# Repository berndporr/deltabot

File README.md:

# The Delta Bot

## What is the Delta Bot?
The Delta Bot is an open-source DIY robot AI platform that uses Radxa's single board computer, 

 - the [Rock 5B+](https://radxa.com/products/rock5/5b/),
 - Parallax's [Continuous Rotation Servo Motors](https://www.parallax.com/product/parallax-continuous-rotation-servo-factory-centered/),
 - C1 LIDAR https://github.com/berndporr/c1lidar and
 - Raspberry PI V2 camera

## Hardware

### Schematics
For details on the DeltaBot schematic, pcb, and footprint library refer to the subfolder [schematic_files](schematic_files).

### Connectors

Plug the right motor into J4, the left motor into J3 and the LIDAR into J2.

### Additional Mechanical Parts
Additional Mechanical Parts were designed in CAD and can be accessed [here](additional_files/deltabot.f3z):

In particular the "stage" which holds the power bank.

## Software

### Install ARMbian

Download from
https://www.armbian.com/rock-5b/
the image "Armbian 25.8.2 Bookworm Minimal / IOT".
the 
Call `armbian-config`:
  - upgrade to Debian "trixie"
  - Make sure you have kernel 26.2.1 Armbian Linux vendor headers 6.1.115-vendor-rk35xx

### PWM motor drivers

Start `sudo nano /boot/armbianEnv.txt`, identify these lines and add/edit them that
they look like these:

```
console=display
overlay_prefix=
overlays=rk3588-pwm14-m0 rk3588-pwm8-m0
```

This enables the UART and PWM on the pins 33 and 34 on the 40 pin header.

Create the group `gpio`:

```
groupadd gpio
```
and add yourself and other users to it who want to write to the PWM device.

Copy the file [90-gpio.rules](90-gpio.rules) to `/etc/udev/rules.d/`. This will
make sure that the PWM can accessed by any user who's in the gpio group.

The library and example programs how to control the motors are in [wheeleddrive](wheeleddrive).

### LIDAR

Enable the UART for serial communication. Start `sudo nano /boot/armbianEnv.txt`, identify these lines and add `rk3588-uart2-m0` to overlays.

```
overlay_prefix=
overlays=rk3588-uart2-m0
```

Add yourself to the group `dialout` to access /dev/tty*.

The driver and example programs are here: https://github.com/berndporr/c1lidar

### Raspberry PI V2 Cameras

The 1st RPI V2 camera has already a device overlay (`rock-5b-rpi-camera-v2`). The device overlay for the 2nd camera
needs to be compiled from source:

```
cpp -nostdinc -I /usr/src/linux-headers-6.1.115-vendor-rk35xx/include/ -undef -x assembler-with-cpp rock-5b-plus-cam1-rpi-camera-v2.dts > cam1.dts
dtc -@ -I dts -O dtb -o /tmp/rock-5b-plus-cam1-rpi-camera-v2.dtbo cam1.dts
cp /tmp/rock-5b-plus-cam1-rpi-camera-v2.dtbo /boot/dtb-6.1.115-vendor-rk35xx/rockchip/overlay/
```

Add this to the overlays in `armbianEnv.tex`:
```
overlays=rk3588-pwm14-m0 rk3588-pwm8-m0 rk3588-uart2-m0 rock-5b-rpi-camera-v2 rock-5b-plus-cam1-rpi-camera-v2
```

and reboot.

If all goes well both cameras will show up as:

```
media-ctl -p -d 0

rkcif (platform:rkcif-mipi-lvds2):
	/dev/video0
	/dev/video1
...
	/dev/media0

rkcif (platform:rkcif-mipi-lvds4):
	/dev/video11
	/dev/video12
...
	/dev/video21
	/dev/media1
```

which are the raw devices outputting Bayer patterns. The media device 1 is for the 2nd camera raw processing chain.

The media devices 2 and 3 are the Image Signal Processing chains which decode the images into YUV or Grey images.

To config the cameras you need to config V4L subdevices:

```
v4l2-ctl --device=/dev/v4l-subdev2 -L
v4l2-ctl --device=/dev/v4l-subdev7 -L

User Controls

                       exposure 0x00980911 (int)    : min=0 max=4095 step=1 default=1575 value=1575
                           gain 0x00980913 (int)    : min=256 max=43663 step=1 default=256 value=21960
                horizontal_flip 0x00980914 (bool)   : default=0 value=1
                  vertical_flip 0x00980915 (bool)   : default=0 value=1
```

[See the demo dual camera viewer](opencv-camera-callback) how it's all done in C++!

A fixed two-camera mount for repeatable stereo geometry is available in
[additional_files/stereo_camera_mount](additional_files/stereo_camera_mount).

The dual-camera viewer also applies a colour correction for the ROCK 5 Raspberry Pi Camera V2 setup.

## Credits
- Saleh AlMulla - 2721704A@student.gla.ac.uk
- Bernd Porr -  bernd.porr@glasgow.ac.uk
- Yixuan Zha - 2974642Z@student.gla.ac.uk

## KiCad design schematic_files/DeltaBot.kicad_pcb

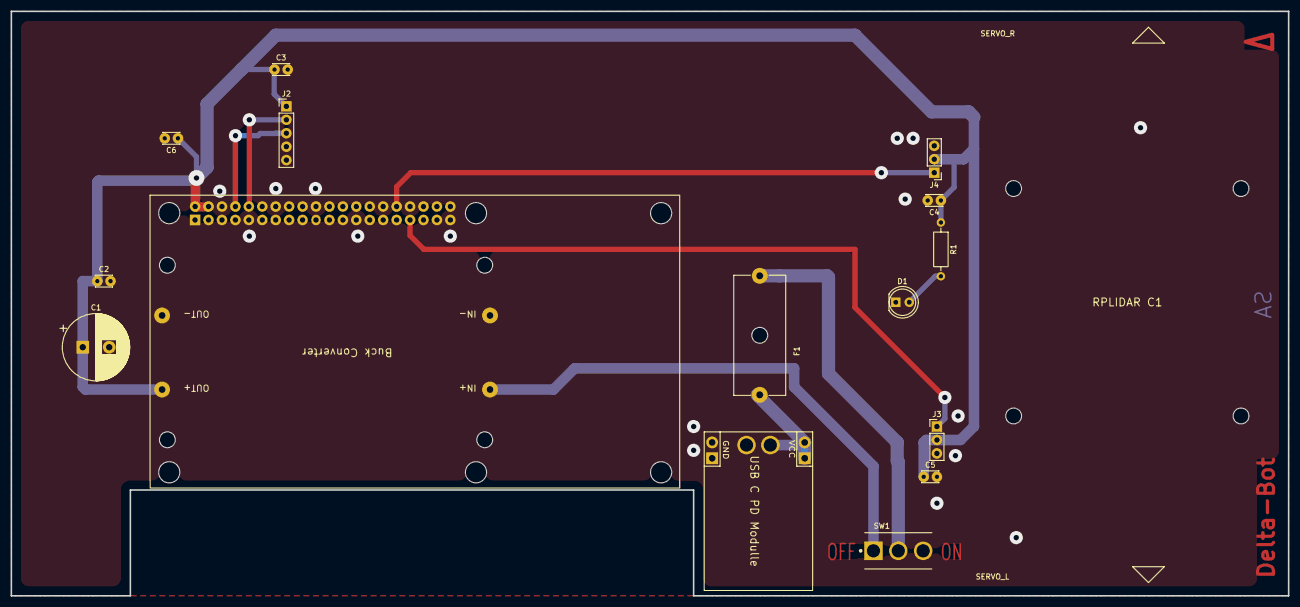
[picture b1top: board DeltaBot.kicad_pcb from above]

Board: 2 copper layers, 241.5 x 110.5 mm, 17 parts (1 on the bottom side), 10 nets.

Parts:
C1: 2200uF; CP_Radial_D12.5mm_P5.00mm
C2, C3, C4, C5, C6: 1uF; C_Disc_D3.0mm_W2.0mm_P2.50mm
D1: LED; LED_D5.0mm_Clear
F1: Fuse; Fuseholder_Cylinder-5x20mm_Schurter_0031_8201_Horizontal_Op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
J1: USB C PD Modulle; USB_C
J2: Conn_01x05; PinHeader_1x05_P2.54mm_Vertical
J3: MOTOR_L; PinHeader_1x03_P2.54mm_Vertical
J4: MOTOR_R; PinHeader_1x03_P2.54mm_Vertical
R1: 330R; R_Axial_DIN0207_L6.3mm_D2.5mm_P10.16mm_Horizontal
SW1: SW_SPDT; TE_4-1825136-5
U1: RPLIDAR C1
U1#2: Radxa_ROCK5B; ROCK_5B
U2: Buck Converter; BUCK_CONV

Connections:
+5V: C1.1, C2.1, C3.1, C4.1, C5.1, C6.1, J2.1, J3.2, J4.2, R1.1, U1#2.2 (5V1), U1#2.4 (5V2), U2.3 (OUT+)
+9V: SW1.1 (A), U2.1 (IN+)
GND: C1.2, C2.2, C3.2, C4.2, C5.2, C6.2, D1.1 (K), J1.2 (GND), J1.4 (GND), J2.4, J3.3, J4.3, U1#2.6 (GND1), U1#2.9 (GND8), U1#2.14 (GND2), U1#2.20 (GND3), U1#2.25 (GND7), U1#2.30 (GND4), U1#2.34 (GND5), U1#2.39 (GND6), U2.2 (IN-), U2.4 (OUT-)
LIDAR_RX: J2.3, U1#2.8 (GPIO4_C3)
LIDAR_TX: J2.2, U1#2.10 (GPIO4_C4)
unnamed: D1.2 (A), R1.2
unnamed: F1.2, J1.1 (VCC), J1.3 (VCC)
unnamed: F1.1, SW1.2 (B)
PWM_L: J3.1, U1#2.33 (GPIO2_B4)
PWM_R: J4.1, U1#2.32 (GPIO3_C0)

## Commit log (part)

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2026-02-01 Got rid of the scripts
2026-02-01 Added new photo
2026-02-01 Removed old files
2026-02-01 Removed the camera bits
2026-02-01 Added info of how to add the C1 LIDAR.
2026-02-01 Fixed the camera texts.
2026-02-01 Fixed the PCB file
2026-02-01 Removed the Schematic from the front page
2026-03-21 Added differential drive class to it.
2026-03-21 Added udev rule
2026-04-01 Added camera howto
2026-04-05 Updated PCB layout
2026-04-06 Small changes
2026-04-06 Added C1 LIDAR to the footprints.
2026-04-06 Fixed the Rock5B footprint which was slightly off.
2026-04-07 Added files for GU manufacture
2026-04-07 Updated the PCB according to Andrew's feedback.
2026-04-07 Updated the gerbers
2026-04-07 Updated the pads of the 40pin Rock5 header to 2mm pad size.
2026-04-10 Updated the PCB so that all pads can be soldered without plating through.
2026-04-10 Added an LED to it.
2026-04-10 Added the stereo viewer
2026-04-10 Now the image is flipped properly.
2026-04-10 Adding a readme
2026-04-10 Adding front view
2026-04-10 Done some re-formatting with vscode
2026-04-10 Added more info about the cameras.
2026-04-11 Added framerate request.
2026-04-11 Added missing file
2026-04-11 Fixed the USB PD module footprint.
2026-04-11 Found a format which gives colour (though with terrible white balance)
2026-04-12 Removed old stuff
2026-04-12 Added missing pics
2026-04-12 Added connectors.
2026-04-12 Consistent where the plug in info is.
2026-04-12 Added info for further reading.
2026-04-12 Added the symbol library table
2026-04-12 Updated the DollaTek Buck converter.
2026-04-29 Added clang format config
